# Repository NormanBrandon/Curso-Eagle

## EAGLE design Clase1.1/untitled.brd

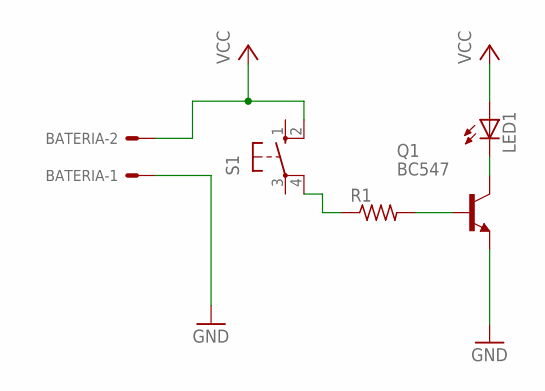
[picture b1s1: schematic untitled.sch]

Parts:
BATERIA: KK-156-2
LED1: LED5MM
Q1: BC547; TO92
R1: R-US_0207/7; 0207/7
S1: 10-XX; B3F-10XX

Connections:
GND: BATERIA.1, Q1.1 (E)
unnamed: Q1.2 (B), R1.2
unnamed: LED1.K (C), Q1.3 (C)
unnamed: R1.1, S1.4 (P1)
VCC: BATERIA.2, LED1.A, S1.2 (S1)

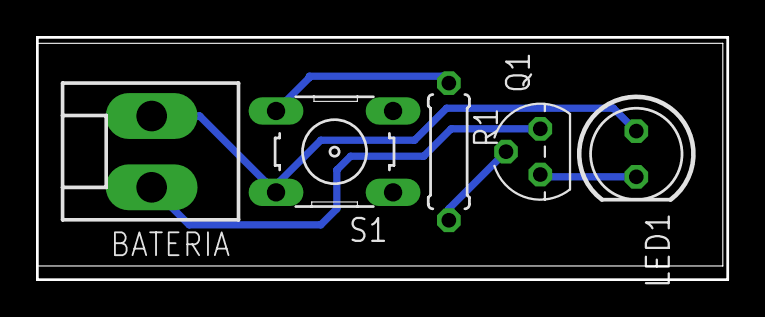
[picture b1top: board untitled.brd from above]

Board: 2 copper layers, 38.4 x 13.5 mm, 5 parts (0 on the bottom side), 5 nets.

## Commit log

2018-09-14 Primera clase Introductoria
